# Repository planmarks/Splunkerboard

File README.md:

# Splunkerboard

**A handheld development and prototyping platform for the Seeed Studio XIAO ESP32 family.**

Splunkerboard puts the things most handheld projects need on one PCB: a 0.96" 128×64 OLED, a six-button D-pad, a LiPo connector with a power switch and, on Splunkerboard 1, a microSD slot, an I/O expander, a battery fuel gauge and breakout headers. Solder on a XIAO ESP32 module (C3, C5, C6, S3 …), plug in USB-C, and start writing firmware.

The schematics, PCB layouts, fabrication files and firmware are all open.

*Designed by Papathought, Tallinn, Estonia (muru.global).*

---

## Contents

| Section | What's in it |
|---|---|
| [Hardware overview](docs/hardware/README.md) | Board variants, what's different between them, I²C map |
| [Splunkerboard 1 (V1C)](docs/hardware/splunkerboard-1.md) | Full variant: MCP23017, MAX17048, microSD, 4-layer PCB |
| [Splunkerboard Dev / DIY (V1B)](docs/hardware/splunkerboard-dev.md) | Compact 2-layer variant: buttons wired straight to the XIAO |
| [Expansion board](docs/hardware/expansion-board.md) | Prototyping add-on board with power rails and pass-through headers |
| [Manufacturing & assembly](docs/hardware/manufacturing.md) | Gerbers, BOM, assembly order, 3D models and case |
| [Firmware overview](docs/firmware/README.md) | Toolchain setup and which firmware runs on which board |
| [Firmware development guide](docs/firmware/development-guide.md) | Pin maps and working code for buttons, OLED, SD and fuel gauge |
| [Sentinel cold wallet](docs/firmware/sentinel-wallet.md) | Air-gapped multi-coin hardware wallet firmware |
| [Gamecard](docs/firmware/gamecard.md) | Retro game console with ESP-NOW multiplayer |
| [WarPet (Wormagotchi)](docs/firmware/warpet.md) | Wardriving virtual pet (passive Wi-Fi/BLE survey) |

---

## Board variants at a glance

| | **Splunkerboard Dev (V1B)** | **Splunkerboard 1 (V1C)** |
|---|---|---|
| Folder | [`Splunkerboard DIY/`](Splunkerboard%20DIY) | [`Splunker 1/`](Splunker%201) |
| PCB | 2-layer, 1.6 mm FR-4 | 4-layer, 1.6 mm FR-4 |
| Size | 47.1 × 79.4 mm | 47.1 × 79.4 mm |
| MCU | XIAO ESP32-C3 / C5 / C6 / S3 (dual footprint: C3 and C5 pad layouts) | same |
| Display | 0.96" SSD1306 OLED **module** (4-pin, I²C `0x3C`) | 0.96" SSD1306 OLED **bare panel** (30-pin FPC, I²C `0x3C`) |
| Buttons | 6, wired directly to XIAO GPIOs | 6, on an **MCP23017** I/O expander (I²C `0x20`) with interrupt |
| Storage | — | **microSD** (SPI) with card-detect |
| Battery gauge | — | **MAX17048** fuel gauge (I²C `0x36`) |
| Breakouts | 2.0 mm pads: D6, D7, D10, power, I²C | 2.54 mm headers: 16 expander I/O, D1/D3/D6/D7, I²C, power |
| Antenna | Optional u.FL → edge-SMA footprint | Uses the XIAO module's own antenna |
| Firmwares in this repo | All three run as-is | Need a port (see [compatibility](docs/firmware/README.md#board-compatibility)) |

## Firmware at a glance

| Firmware | Folder | Target | Summary |
|---|---|---|---|
| **Sentinel** (cold wallet) | [`Firmwares/Crypto Wallet`](Firmwares/Crypto%20Wallet) | XIAO ESP32-C5 | BIP39 seed, PIN-encrypted storage, offline signing for BTC, ETH and EVM chains, SOL, XLM, ADA, XRP, ATOM, TRX, TON |
| **Gamecard** | [`Firmwares/Gamecard/gamecard`](Firmwares/Gamecard/gamecard) | XIAO ESP32-C3 | 12 games, including 2–4 player Pong, Tron, Battleship and Uno over ESP-NOW |
| **WarPet** | [`Firmwares/Wormagotchi`](Firmwares/Wormagotchi) | XIAO ESP32-C5 | Virtual pet that levels up from passive dual-band Wi-Fi + BLE discoveries |

> **Naming:** the KiCad files use the project's working name **"Spunkleboard"**, and early Dev gerbers are named **"ESP32C5 Cold Wallet"**. These all refer to Splunkerboard.

## Tools used

| Tool | Used for |
|---|---|
| [KiCad](https://www.kicad.org/) 10 | Schematics, PCB layout, gerbers |
| [Blender](https://www.blender.org/) | Renders, 3D mock-ups, enclosure |
| Arduino IDE / arduino-cli (esp32 core 3.x) | Firmware |
| [Lopaka](https://lopaka.app/) | OLED UI mock-ups (WarPet) |

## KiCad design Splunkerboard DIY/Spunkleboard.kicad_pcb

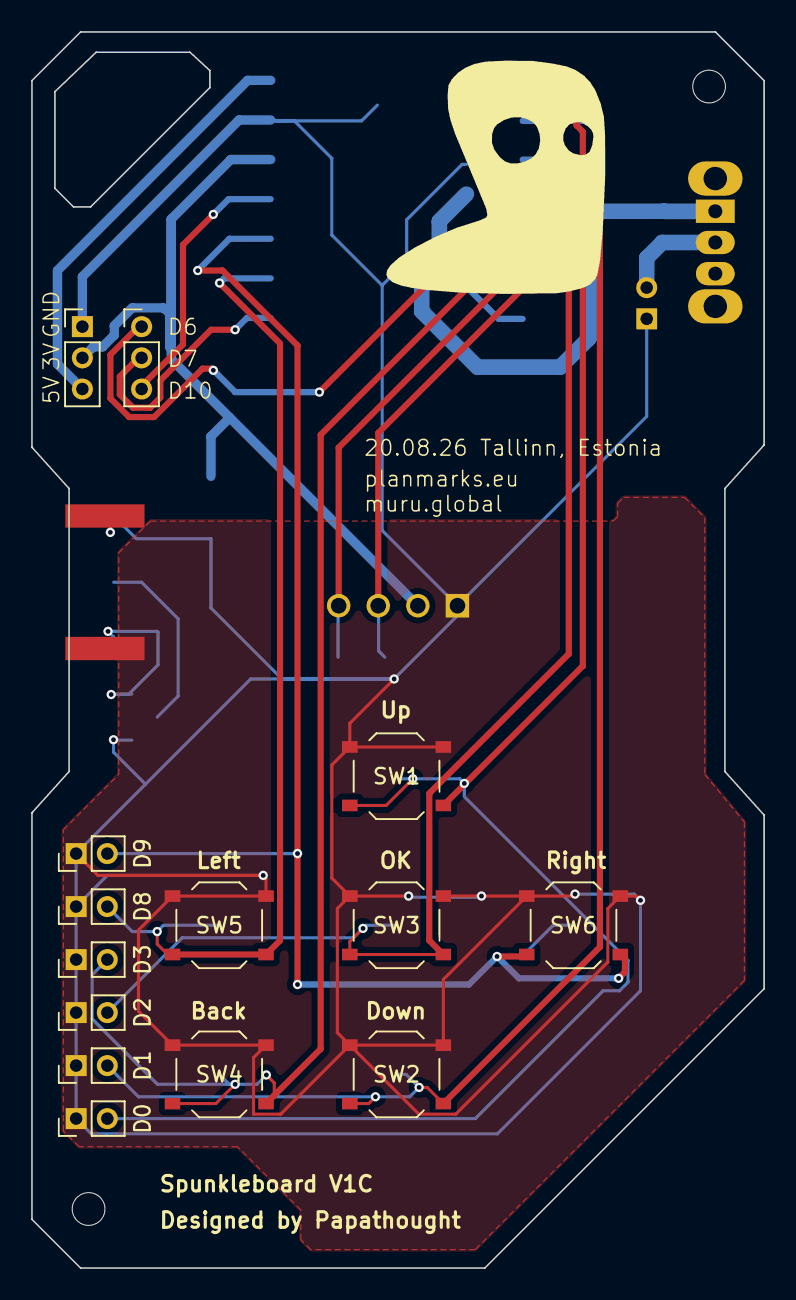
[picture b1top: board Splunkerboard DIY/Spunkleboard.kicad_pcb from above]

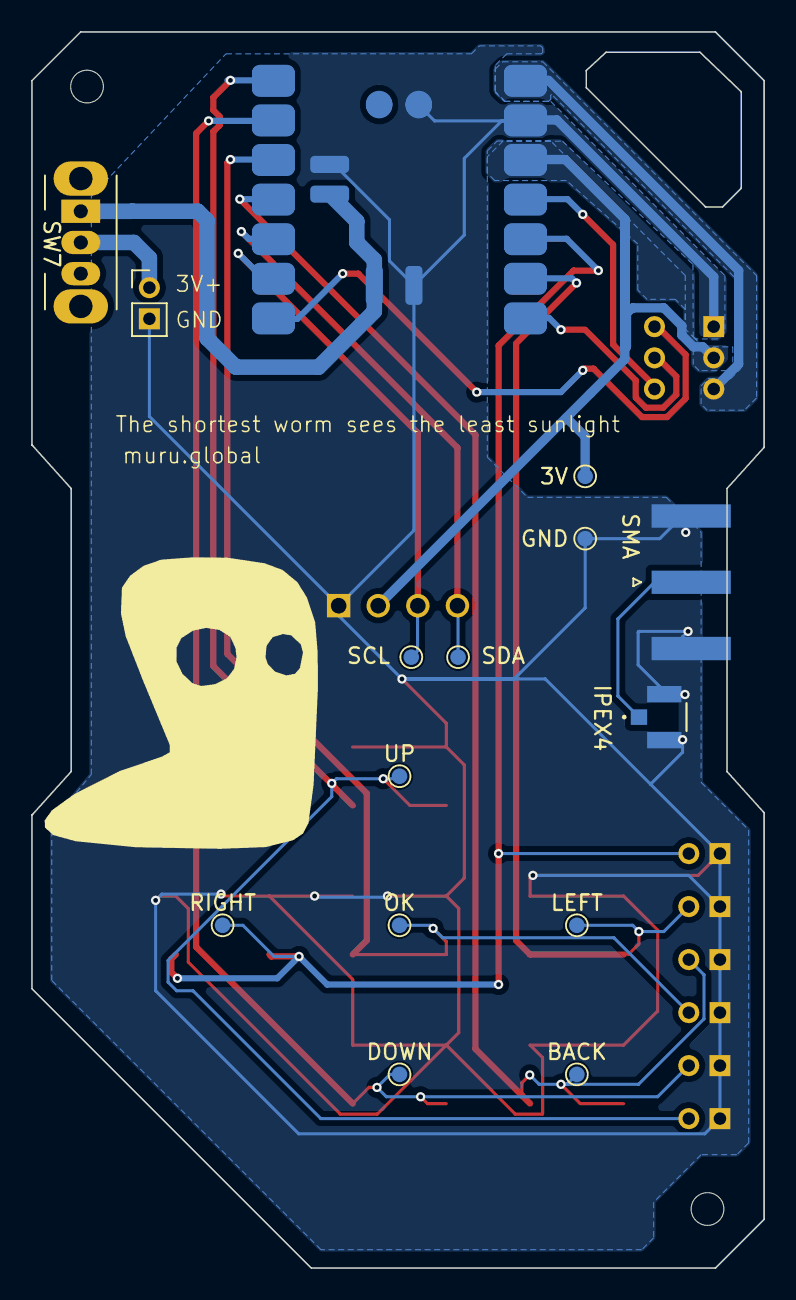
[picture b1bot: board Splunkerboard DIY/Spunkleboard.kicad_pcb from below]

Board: 2 copper layers, 47.0 x 79.3 mm, 31 parts (16 on the bottom side), 18 nets.

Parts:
3V: 3V3; TestPoint_Pad_D1.0mm
BACK: SW-BCK; TestPoint_Pad_D1.0mm
BT1: Battery; PinHeader_1x02_P2.00mm_Vertical
D0, D1, D2, D3, D8, D9: PinHeader_1x02_P2.00mm_Vertical
DOWN: SW-DWN; TestPoint_Pad_D1.0mm
GND: GND; TestPoint_Pad_D1.0mm
IPEX4: MHF_I_RECE_IPX; MHF I_RECE_IPX
LEFT: SW-LFT; TestPoint_Pad_D1.0mm
MNT: MountingHole_2.1mm
MNT#2: MountingHole_2.1mm
OK: SW-OK; TestPoint_Pad_D1.0mm
RIGHT: SW-RHT; TestPoint_Pad_D1.0mm
SCL: SCL; TestPoint_Pad_D1.0mm
SDA: SDA; TestPoint_Pad_D1.0mm
SMA: SMA_Amphenol_132289_EdgeMount
SW1: SW_Push UP; SW_Push_1P1T_XKB_TS-1187A
SW2: SW_Push DOWN; SW_Push_1P1T_XKB_TS-1187A
SW3: SW_Push OK; SW_Push_1P1T_XKB_TS-1187A
SW4: SW_Push BACK; SW_Push_1P1T_XKB_TS-1187A
SW5: SW_Push LEFT; SW_Push_1P1T_XKB_TS-1187A
SW6: SW_Push RIGHT; SW_Push_1P1T_XKB_TS-1187A
SW7: SW_SPDT; SW_Slide_SPDT_Angled_CK_OS102011MA1Q
U1: XIAO-ESP32-C5-SMD
U2: DM-OLED096-636; MODULE_DM-OLED096-636
U3: XIAO-ESP32-C3-SMD
UP: SW-UP; TestPoint_Pad_D1.0mm

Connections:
+3.3V: 3V.1 (1_1), U1.12 (3V3_OUT), U2.2 (VCC_IN), U3.12 (3V3_OUT)
BAT+: BT1.1 (+), SW7.2 (B)
D0-SW1: D0.2, SW1.2, U1.1 (D0), U3.1 (D0), UP.1 (1_1)
D1-SW2: D1.2, DOWN.1 (1_1), SW2.2, U1.2 (D1), U3.2 (D1)
D2-SW3: D2.2, OK.1 (1_1), SW3.2, U1.3 (D2), U3.3 (D2)
D3-SW4: BACK.1 (1_1), D3.2, SW4.2, U1.4 (D3), U3.4 (D3)
D4-SDA: SDA.1 (1_1), U1.5 (D4), U2.4 (SDA), U3.5 (D4)
D5-SCL: SCL.1 (1_1), U1.6 (D5), U2.3 (SCL), U3.6 (D5)
D6: U1.7 (D6), U3.7 (D6)
D7: U1.8 (D7), U3.8 (D7)
D8-SW5: D8.2, LEFT.1 (1_1), SW5.2, U1.9 (D8), U3.9 (D8)
D9-SW6: D9.2, RIGHT.1 (1_1), SW6.2, U1.10 (D9), U3.10 (D9/BOOT)
D10: U1.11 (D10), U3.11 (D10)
EN: U1.17 (EN), U3.17 (EN)
GND: BT1.2 (-), D0.1, D1.1, D2.1, D3.1, D8.1, D9.1, GND.1 (1_1), IPEX4.1, IPEX4.2, SMA.2, SW1.1, SW2.1, SW3.1, SW4.1, SW5.1, SW6.1, U1.13 (GND), U1.18 (GND), U1.24 (GND), U2.1 (GND), U3.13 (GND), U3.18 (GND), U3.22 (GND)
IPEX: IPEX4.3, SMA.1
VBAT: SW7.1 (A), U1.23 (VBAT), U3.21 (VBAT)
VBUS: U1.14 (VBUS), U3.14 (VBUS)

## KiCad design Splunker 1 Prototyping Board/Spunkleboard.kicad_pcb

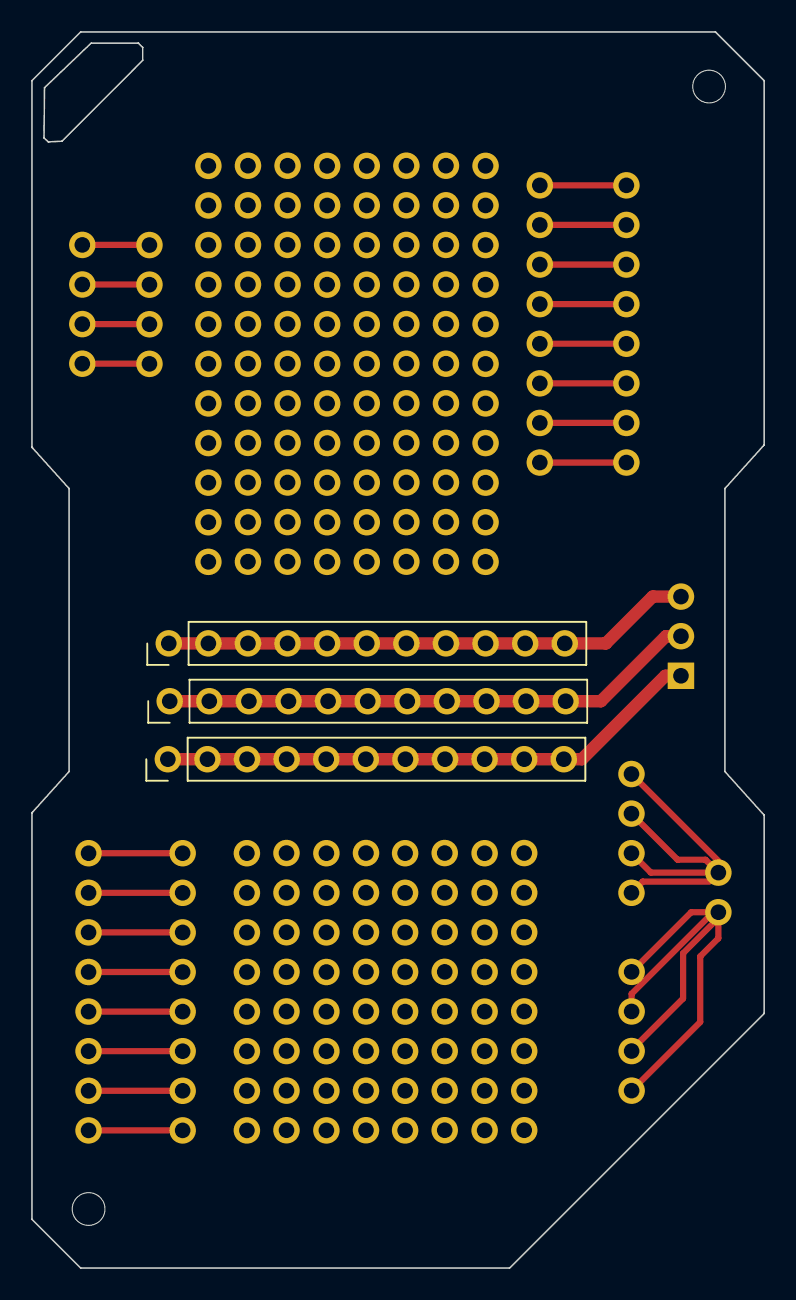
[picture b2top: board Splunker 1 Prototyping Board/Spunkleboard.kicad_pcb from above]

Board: 4 copper layers, 47.0 x 79.3 mm, 5 parts (0 on the bottom side), 3 nets.

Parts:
3V, 5V: PinHeader_1x11_P2.54mm_Vertical
GND: PinHeader_1x11_P2.54mm_Vertical
MNT: MountingHole_2.1mm
MNT#2: MountingHole_2.1mm

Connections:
+3V3: 3V.1, 3V.2, 3V.3, 3V.4, 3V.5, 3V.6, 3V.7, 3V.8, 3V.9, 3V.10, 3V.11
GND: GND.1, GND.2, GND.3, GND.4, GND.5, GND.6, GND.7, GND.8, GND.9, GND.10, GND.11
VBUS: 5V.1, 5V.2, 5V.3, 5V.4, 5V.5, 5V.6, 5V.7, 5V.8, 5V.9, 5V.10, 5V.11

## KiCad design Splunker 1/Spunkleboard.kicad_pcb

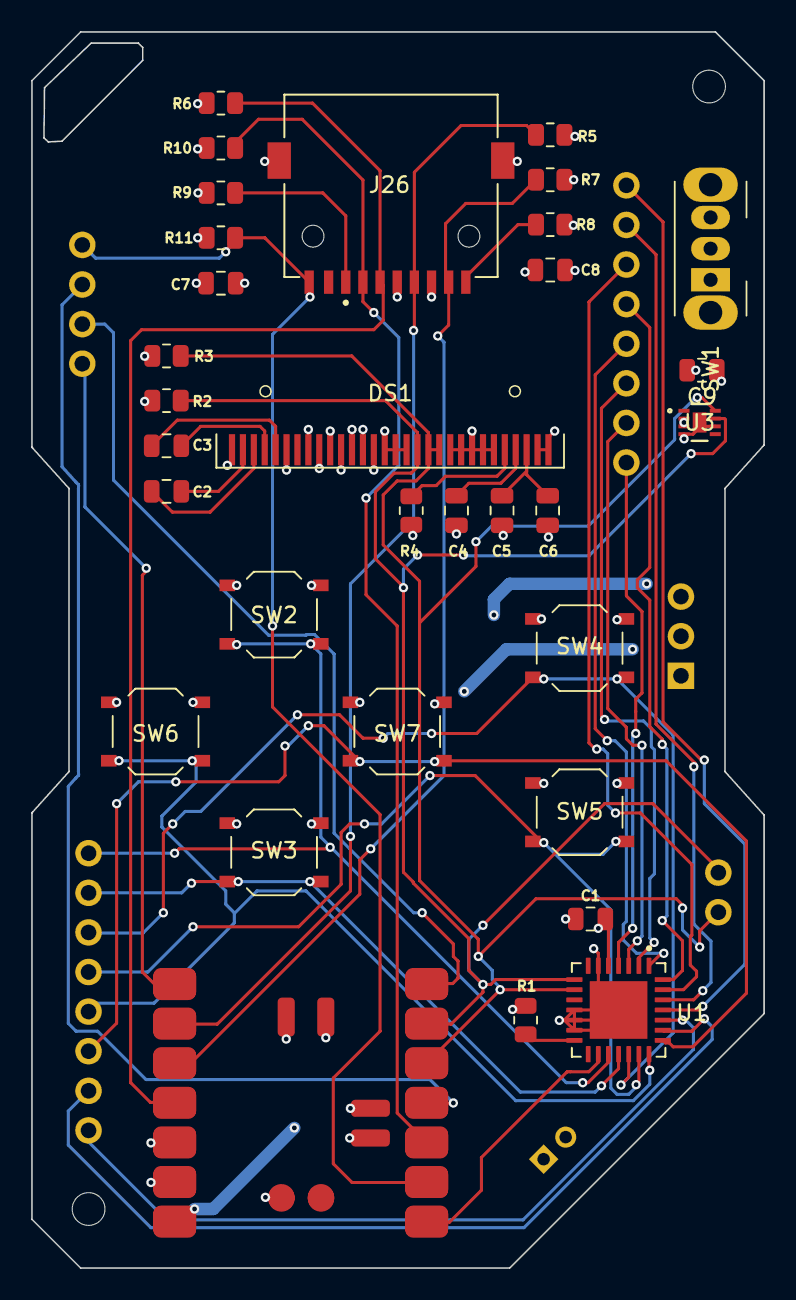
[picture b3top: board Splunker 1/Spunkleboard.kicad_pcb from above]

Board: 4 copper layers, 47.0 x 79.3 mm, 36 parts (1 on the bottom side), 33 nets.

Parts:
BT1: Battery; PinHeader_1x02_P2.00mm_Vertical
C1, C5, C8, C9: 0.1uF; C_0805_2012Metric
C2, C3: 2.2 µF; C_0805_2012Metric
C4: 1uF; C_0805_2012Metric
C6: 2uF; C_0805_2012Metric
C7: 10uF; C_0805_2012Metric
DS1: OLED-128O064D
J26: MSD-11-A; CUI_MSD-11-A
MNT: MountingHole_2.1mm
MNT#2: MountingHole_2.1mm
R1: 10K; R_0805_2012Metric
R2, R3, R5, R6, R7, R8, R9, R10, R11: 4.7K; R_0805_2012Metric
R4: 390K; R_0805_2012Metric
SW1: SW_SPDT; SW_Slide_SPDT_Angled_CK_OS102011MA1Q
SW2: SW_Push UP; SW_Push_1P1T_XKB_TS-1187A
SW3: SW_Push DOWN; SW_Push_1P1T_XKB_TS-1187A
SW4: SW_Push OK; SW_Push_1P1T_XKB_TS-1187A
SW5: SW_Push BACK; SW_Push_1P1T_XKB_TS-1187A
SW6: SW_Push LEFT; SW_Push_1P1T_XKB_TS-1187A
SW7: SW_Push RIGHT; SW_Push_1P1T_XKB_TS-1187A
U1: XIAO-ESP32-C5-SMD
U1#2: MCP23017-EML; QFN65P600X600X100-29N
U3: MAX17048G+T10; 21-0168E_T822-3_MXM
U3#2: XIAO-ESP32-C3-SMD

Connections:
+3V3: C1.2, C7.1, C8.1, DS1.6 (VBAT), DS1.9 (VDD), DS1.11 (BS1), DS1.14 (~RES), J26.P4 (VDD), R1.1, R2.1, R3.1, R5.2, R6.2, R7.2, R8.2, R9.2, R10.2, R11.2, U1.12 (3V3_OUT), U1#2.5 (VDD), U3#2.12 (3V3_OUT)
D0-INTA: U1.1 (D0), U1#2.16 (INTA), U3#2.1 (D0)
D1: J26.CD, R11.1, U1.2 (D1), U3#2.2 (D1)
D2-SDCS: J26.P2 (CD/DAT3), R10.1, U1.3 (D2), U3#2.3 (D2)
D3: U1.4 (D3), U3#2.4 (D3)
D4-SDA: DS1.19 (D1), DS1.20 (D2), R3.2, U1.5 (D4), U1#2.9 (SDA), U3.8 (SDA), U3#2.5 (D4)
D5-SCL: DS1.18 (D0), R2.2, U1.6 (D5), U1#2.8 (SCK), U3.7 (SCL), U3#2.6 (D5)
D6: U1.7 (D6), U3#2.7 (D6)
D7: U1.8 (D7), U3#2.8 (D7)
D8-SDCLK: J26.P5 (CLK), R5.1, U1.9 (D8), U3#2.9 (D8)
D9-SDSO: J26.P7 (DAT0), R7.1, U1.10 (D9), U3#2.10 (D9/BOOT)
D10-SDSI: J26.P3 (CMD), R6.1, U1.11 (D10), U3#2.11 (D10)
EN: U1.17 (EN), U3#2.17 (EN)
GND: BT1.2 (-), C1.1, C4.2, C5.2, C6.2, C7.2, C8.2, C9.1, DS1.1 (GND), DS1.8 (VSS), DS1.10 (BS0), DS1.12 (BS2), DS1.13 (~CS), DS1.15 (D/~C), DS1.16 (R/~W), DS1.17 (E/~RD), DS1.21 (D3), DS1.22 (D4), DS1.23 (D5), DS1.24 (D6), DS1.25 (D7), DS1.29 (VLSS), DS1.30 (GND), J26.G1 (COVER_GND), J26.G2 (COVER_GND), J26.P6 (VSS), R4.1, SW2.1, SW3.1, SW4.1, SW5.1, SW6.1, SW7.1, U1.13 (GND), U1.18 (GND), U1.24 (GND), U1#2.6 (VSS), U1#2.11 (A0), U1#2.12 (A1), U1#2.13 (A2), U1#2.29 (EXP), U3.4 (GND), U3.6 (QSTRT), U3.9 (EPAD), U3#2.13 (GND), U3#2.18 (GND), U3#2.22 (GND)
unnamed: C3.1, DS1.5 (C1N)
unnamed: C3.2, DS1.4 (C1P)
unnamed: C2.2, DS1.2 (C2N)
unnamed: C2.1, DS1.3 (C2P)
unnamed: DS1.26 (IREF), R4.2
unnamed: C5.1, C6.1, DS1.28 (VCC)
unnamed: C4.1, DS1.27 (VCOMH)
unnamed: J26.P8 (DAT1), R8.1
unnamed: J26.P1 (DAT2), R9.1
unnamed: R1.2, U1#2.14 (~RESET)
PWR: SW1.2 (B), U1.23 (VBAT), U3#2.21 (VBAT)
SW2-GPA0: SW2.2, U1#2.17 (GPA0)
SW3-GPA1: SW3.2, U1#2.18 (GPA1)
SW4-GPA2: SW4.2, U1#2.19 (GPA2)
SW5-GPA3: SW5.2, U1#2.20 (GPA3)
SW6-GPA4: SW6.2, U1#2.21 (GPA4)
SW7-GPA5: SW7.2, U1#2.22 (GPA5)
VBAT: BT1.1 (+), C9.2, SW1.3 (C), U3.2 (CELL), U3.3 (VDD)
VBUS: U1.14 (VBUS), U3#2.14 (VBUS)

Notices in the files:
README.md:
License: not yet chosen
